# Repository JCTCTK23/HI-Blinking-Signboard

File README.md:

#  H I  Blinking Signboard PCB Using an NE555P

## Description
This project showcase how a NE555P works, how to make the schematics of it in KiCAD EDA and how easy is to learn PCB designing using basic electronic components

## Features
- NE555P timer IC module
- Ten LEDs to make the little signboard that says HI
- Powered by 2 wires one with 5v - 7v and the other with Ground

## Visual Overview

## Components List
- NE555 Timer IC x 1
- 330Ω Resistors x 10
- 470Ω Resistor x 1
- 1kΩ Resistor x 1
- 740µF Capacitor x 1
- LEDs x 10
- USB Connector x 1

## Assembly Instructions
1. Solder the NE555 timer IC onto the PCB.
2. Attach each LED and corresponding resistor.
3. Connect the wires in the correct form.
4. Check all connections for any possible short circuits.

## Tools Used
- [KiCAD EDA Software](https://www.kicad.org/)

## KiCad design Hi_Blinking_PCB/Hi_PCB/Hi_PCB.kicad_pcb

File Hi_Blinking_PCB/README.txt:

#  H I  Blinking Signboard PCB Using an NE555P

## Description
This project showcase how a NE555P works, how to make the schematics of it in KiCAD EDA and how easy is to learn PCB designing using basic electronic components

## Features
- NE555P timer IC module
- Ten LEDs to make the little signboard that says HI
- Powered by 2 wires one with 5v - 7v and the other with Ground

## Visual Overview

## Components List
- NE555 Timer IC x 1
- 330Ω Resistors x 10
- 470Ω Resistor x 1
- 1kΩ Resistor x 1
- 740µF Capacitor x 1
- LEDs x 10
- USB Connector x 1

## Assembly Instructions
1. Solder the NE555 timer IC onto the PCB.
2. Attach each LED and corresponding resistor.
3. Connect the wires in the correct form.
4. Check all connections for any possible short circuits.

## Tools Used
- [KiCAD EDA Software](https://www.kicad.org/)

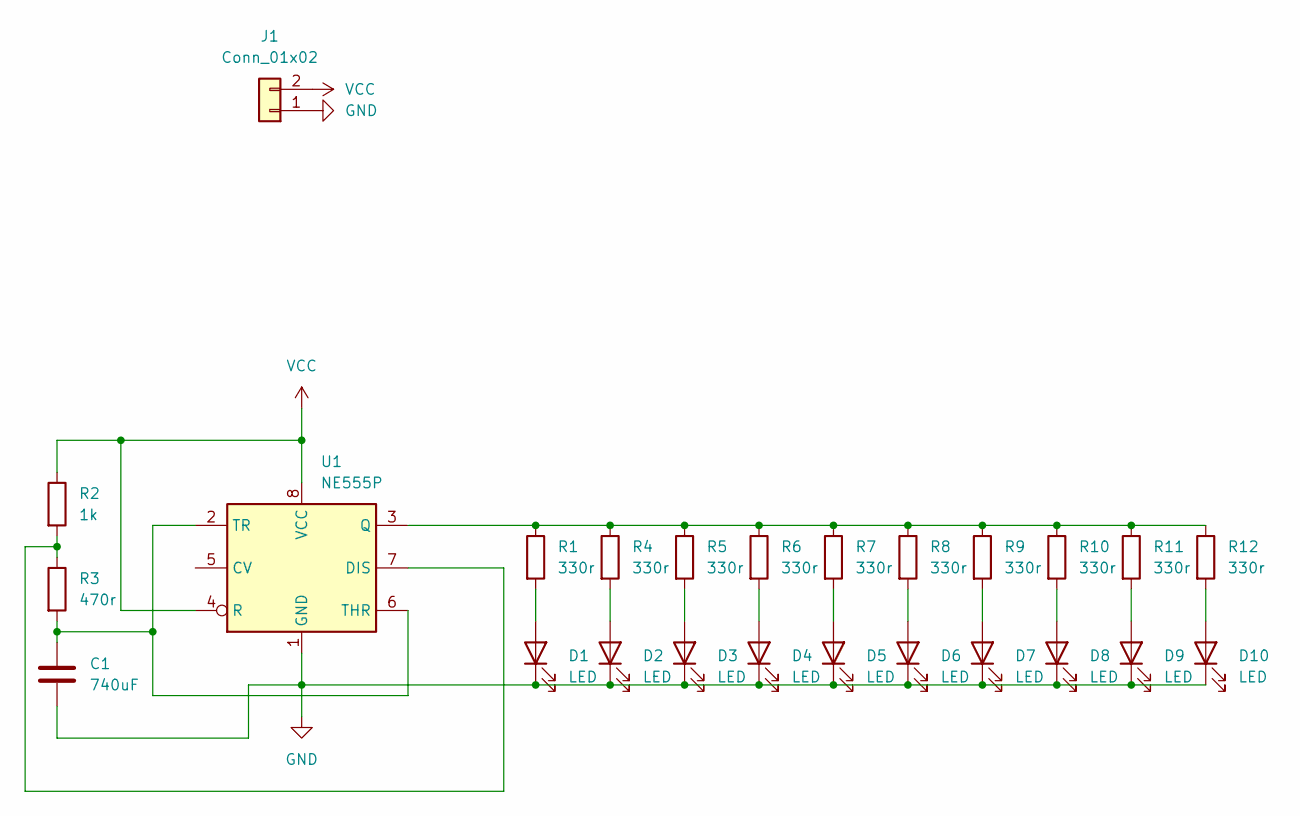
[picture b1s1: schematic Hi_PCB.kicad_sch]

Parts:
C1: 740uF; CP_Axial_L10.0mm_D6.0mm_P15.00mm_Horizontal
D1, D2, D3, D4, D5, D6, D7, D8, D9, D10: LED; LED_D5.0mm
J1: Conn_01x02; PinHeader_1x02_P2.54mm_Vertical
R1, R4, R5, R6, R7, R8, R9, R10, R11, R12: 330r; R_Axial_DIN0204_L3.6mm_D1.6mm_P5.08mm_Horizontal
R2: 1k; R_Axial_DIN0204_L3.6mm_D1.6mm_P5.08mm_Horizontal
R3: 470r; R_Axial_DIN0204_L3.6mm_D1.6mm_P5.08mm_Horizontal
U1: NE555P; DIP-8_W7.62mm

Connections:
GND: C1.1, D1.1 (K), D2.1 (K), D3.1 (K), D4.1 (K), D5.1 (K), D6.1 (K), D7.1 (K), D8.1 (K), D9.1 (K), D10.1 (K), J1.1, U1.1 (GND)
unnamed: D1.2 (A), R1.2
unnamed: D2.2 (A), R4.2
unnamed: D3.2 (A), R5.2
unnamed: D4.2 (A), R6.2
unnamed: D5.2 (A), R7.2
unnamed: D6.2 (A), R8.2
unnamed: D7.2 (A), R9.2
unnamed: D8.2 (A), R10.2
unnamed: D9.2 (A), R11.2
unnamed: D10.2 (A), R12.2
unnamed: R2.2, R3.1, U1.7 (DIS)
unnamed: R1.1, R4.1, R5.1, R6.1, R7.1, R8.1, R9.1, R10.1, R11.1, R12.1, U1.3 (Q)
unnamed: C1.2, R3.2, U1.2 (TR), U1.6 (THR)
VCC: J1.2, R2.1, U1.4 (R), U1.8 (VCC)

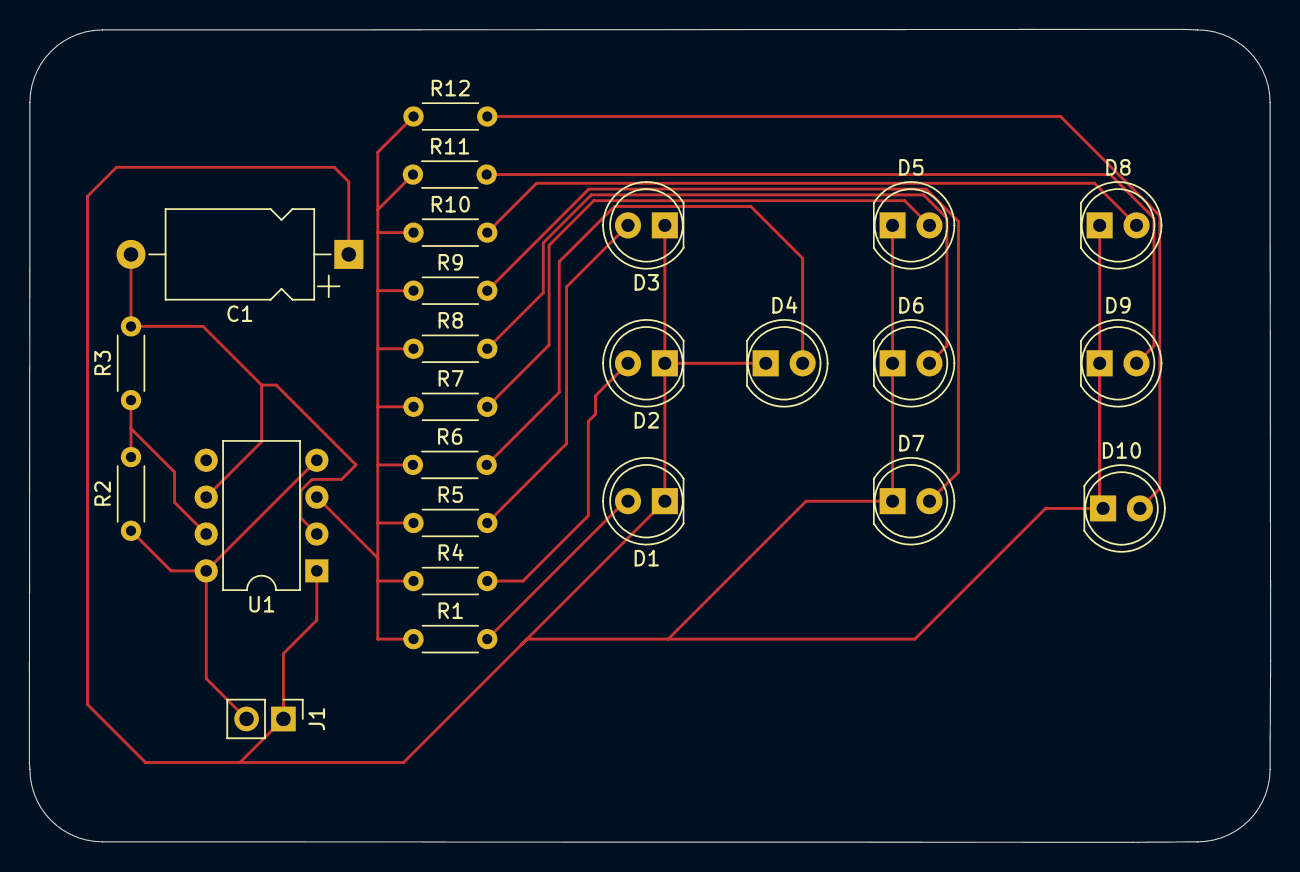
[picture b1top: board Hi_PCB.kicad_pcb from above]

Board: 2 copper layers, 85.5 x 56.0 mm, 25 parts (0 on the bottom side), 15 nets.
